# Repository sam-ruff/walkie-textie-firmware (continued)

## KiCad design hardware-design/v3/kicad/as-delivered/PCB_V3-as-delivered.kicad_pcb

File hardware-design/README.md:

# Hardware design

The board being worked on is the LoRa sensor node in `v3/kicad/` (V3.1). Its
own README says how to rebuild it and what to check before ordering, and
`CE_TESTING.md` beside it is how to run the compliance tests. No board has
been made from it yet.

`v3/` also holds the handover brief and the outside designer's drops that
V3.1 grew from. `archive/` holds the earlier radio boards and the scripts
that rebuilt the first of them. Nothing in there is current.

`CLAUDE.md` is the working log: what is settled and why, and the mistakes
made on the way.

KiCad 9 or newer is needed. The V3.1 tools use KiCad's `pcbnew` Python module
and were written against KiCad 10.0.8.

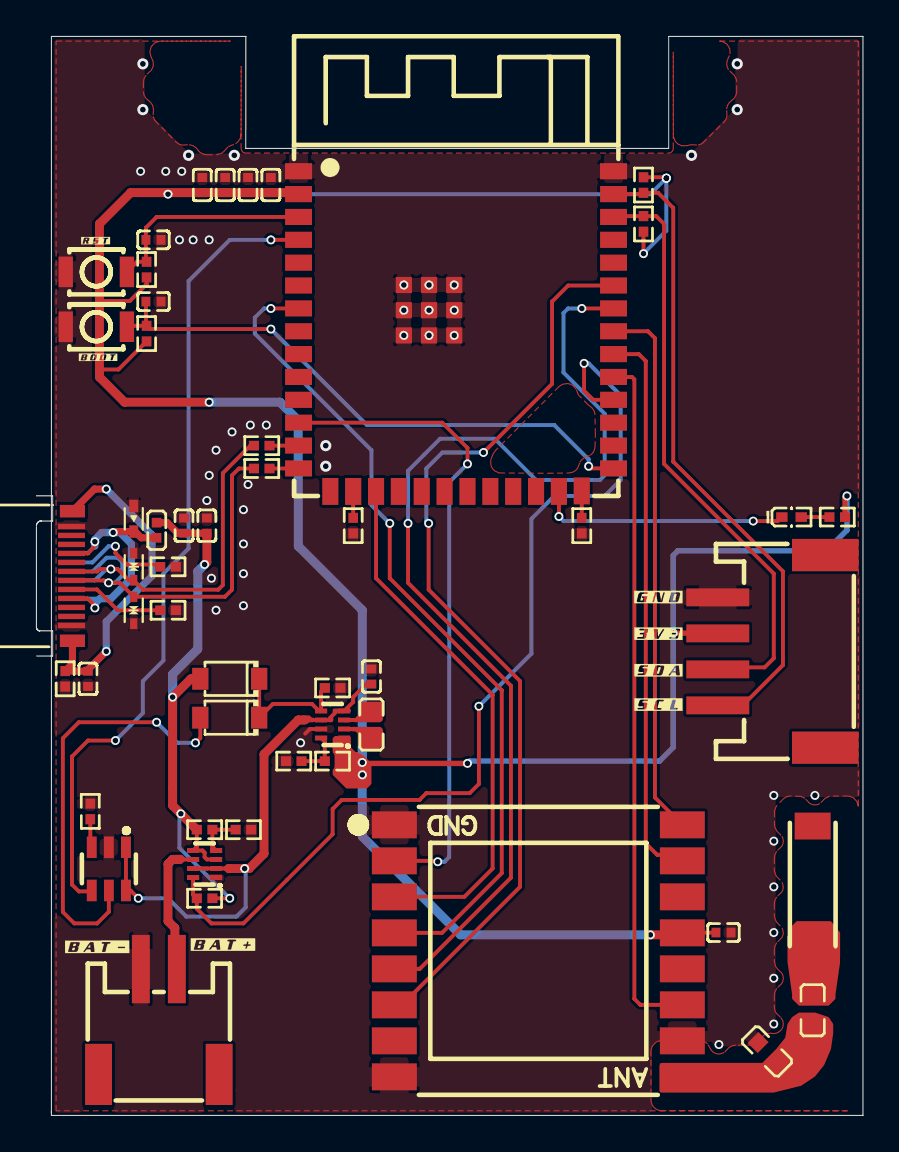
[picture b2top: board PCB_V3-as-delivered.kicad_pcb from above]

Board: 4 copper layers, 45.9 x 59.9 mm, 51 parts (0 on the bottom side), 40 nets.

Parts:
C1: 10uF; C0402
C3, C5, C7, C12, C13: 100nF; C0402
C4, C6, C9: 4.7uF; C0402
C25: 1nF; C0402
CN1: XY-S2B-PH-SM4-TB; CONN-SMD_P2.00_S2B-PH-SM4-TB-LF-SN
D1, D2: LESD5D5.0CT1G_C5199850; SOD-523_L1.2-W0.8-LS1.6-BI
D3: ESD5Z5; SOD-523_L1.2-W0.8-LS1.6-RD-2
L1: W3000; ANT-SMD_L7.0-W1.6
L2: 1uH; L0603
L3: 1KΩ; L0402
L5: 6.8nH; L0603
L6: 39nH; L0603
LED1: SZYY0402B; LED0402-RD_BLUE
R1, R2: 33Ω; R0402
R3, R4: 5.1kΩ; R0402
R5, R6, R8, R11, R12: 10kΩ; R0402
R7: 1kΩ; R0402
R9, R13: 47kΩ; R0402
R10: 1MΩ; R0402
R15: 511kΩ; R0402
R16: 91kΩ; R0402
R18, R19: 4.7kΩ; R0402
R20: 68kΩ; R0402
SW1, SW2: B3U-1000P; KEY-SMD_B3U-1000PM
U1: ESP32-S3-WROOM-1(N8R8); WIRELM-SMD_ESP32-S3-WROOM-1
U2: 1uF; C0402
U3: S4B-PH-SM4-TB(LF)(SN); CONN-SMD_S4B-PH-SM4-TB-LF-SN
U4: TPS2116DRLR; SOT-583-8_L2.1-W1.6-P0.50-LS1.6-BL
U5: TPS631000DRLR; SOT-583-8_L2.1-W1.2-P0.50-LS1.6-BL
U6: 15kΩ; R0402
U7, U9: B5819W_C2848199; SOD-123_L2.7-W1.6-LS3.7-RD
U8: TYPE-C 24P-GTJB 040; USB-C-SMD_TYPE-C-24P-GTJB-040
U10: TPL5111DDCR; TSOT-23-6_L2.9-W1.6-P0.95-LS2.8-BL
U11: SX1262S8S+T-X1; WIRELM-SMD_SX1278S165SY-T-X1

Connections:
3.3V_RAIL: C4.2, C9.2, C12.2, C13.2, R5.1, R6.1, R7.2, R15.2, R18.1, R19.1, U1.2, U2.2, U3.3, U5.1, U11.13
BAT+: CN1.2, U4.6
BOOT: C5.2, R6.2, SW1.1, U1.27
BUSY: U1.33, U11.16
CHS: C25.1, R10.1, U8.25, U8.26
D+: D1.1, R2.1, U8.A6, U8.B6
D-: D2.1, R1.1, U8.A7, U8.B7
DIO1: U1.32, U11.15
DONE: U1.4, U10.4
DRVN: U7.2, U10.5
EN: C3.2, R5.2, SW2.1, U1.3
GND: C1.1, C3.1, C4.1, C5.1, C6.1, C7.1, C9.1, C12.1, C13.1, C25.2, CN1.1, D1.2, D2.2, D3.2, L5.2, R3.1, R4.1, R10.2, R11.1, R12.1, R13.2, R16.2, R20.1, SW1.2, SW2.2, U1.1, U1.40, U1.41, U2.1, U3.4, U4.1, U5.7, U6.1, U8.A1, U8.A12, U8.B1, U8.B12, U10.2, U11.1, U11.8, U11.10
L1_1: L1.1, L6.2
LED1_2: LED1.2, R7.1
MISO: U1.12, U11.2
MOSI: U1.17, U11.3
NSS: U1.34, U11.5
R1_2: R1.2, U1.13
R2_2: R2.2, U1.14
R3_2: R3.2, U8.B5
R4_2: R4.2, U8.A5
RST: U1.35, U11.6
RXE: U1.31, U11.11
SCK: U1.7, U11.4
SCL: R19.2, U1.39, U3.1
SDA: R18.2, U1.38, U3.2
ST: R8.1, U1.30, U4.8
SYS_OUT: C1.2, U4.2, U4.7, U5.4, U5.6, U10.1, U10.6
U1_16: R11.2, U1.16
U1_26: R12.2, U1.26
U4_4: R9.1, U4.4, U6.2
U5_2: L2.2, U5.2
U5_3: L2.1, U5.3
U5_5: R13.1, U5.5, U7.1, U9.1
U5_8: R15.1, R16.1, U5.8
U10_3: R20.2, U10.3
U11_9: L5.1, L6.1, U11.9
USER_LED: LED1.1, U1.25
VBUS: C6.2, C7.2, L3.2, R8.2, R9.2, U4.3, U4.5, U9.2
VBUS_IN: D3.1, L3.1, U8.A4, U8.A9, U8.B4, U8.B9

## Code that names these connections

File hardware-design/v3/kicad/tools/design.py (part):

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part("R40", "1.5k", R0402, (8.75, 38.15), 90, {"1": "ILM", "2": "GND"}, lcsc="C25867", mpn="0402WGF1501TCE", manufacturer="UNI-ROYAL")

# ---------------------------------------------------------------- battery input and power mux
kept("CN1", "CN1", {"1": "BAT_RAW", "2": "GND", "3": "", "4": ""})     # pin order as the brief (B4)
# The brief names Vishay's Si2367DS, which JLCPCB does not stock. The Si2333DS is the same maker's
# 12 V part with the same pinout, and it is specified at the gate drive two tired AA cells give:
# 59 milliohms at 1.8 V, with 100 nA gate leakage.
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# wire-wound part with 0.26 ohms of resistance; the drop's multilayer 39 nH has 1 ohm, a Q of 12 at
# 100 MHz and a self-resonance that can be as low as 1.4 GHz. L5 only shunts the feed, and JLCPCB holds
# no wire-wound 6.8 nH in numbers, so it stays as the drop had it.
kept("L6", "L6", {"1": "ANT_FEED", "2": "RF_FEED"}, at=(32.0, 9.5), rot=90,
     value="39nH", lcsc="C86134", mpn="LQW18AN39NG00D", manufacturer="Murata")
part("L7", "DNP", L0603, (30.3, 9.5), 90, {"1": "ANT_FEED", "2": "GND"}, dnp=True)
part("ANT1", "W3000", (LIB_NEW, "Pulse_W3000"), (35.3, 1.3), 0, {"1": "ANT_FEED", "2": "ANT_TUNE"},
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
    # USB input protection: bead -> C7 and U14's input pins -> U14 -> VBUS
    (T, "VBUS_F", "top", 0.4, [(5.84, 33.297), (5.84, 35.25), (6.85, 35.25)]),
    (T, "VBUS_F", "top", 0.25, [(6.85, 35.25), (6.85, 35.75)]),                                  # both input pins
    (T, "VBUS_F", "top", 0.2, [(5.84, 35.25), (5.84, 35.55), (4.971, 35.55), (4.971, 36.25)]),   # R38
    (T, "UVLO", "top", 0.2, [(5.837, 36.25), (6.85, 36.25)]),
    (T, "UVLO", "top", 0.2, [(5.837, 36.25), (5.837, 37.121)]),                                  # R39
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
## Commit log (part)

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2025-12-06 feat(api): initial commit
2025-12-06 Removed target directory
2025-12-06 fix: Updated rust action
2025-12-06 Notes added by 'git notes add'
2025-12-06 fix: Updated README and made actions skip on chores
2025-12-06 fix: Working BLE implementation and tests
2025-12-06 fix: Made the recieving more reliable and added ble to ble tests
2025-12-14 fix: Minor fixes
2025-12-14 fix: Moved embassy tasks to tasks module
2025-12-14 fix: Working debug logging
2025-12-15 fix: Added debug for version and reboot command and fixed github actions.
2025-12-15 fix: updated README with commands
2025-12-15 fix: Fixed a number of warnings and made clippy happy
2025-12-15 fix: Removed serial module
2025-12-15 fix: Fixed some missing packages and removed log
2025-12-15 fix: Updated how debugging works
2025-12-15 fix: Updated tests and flash devices
2026-06-19 chore(lora): WIP calibration and driver updates
2026-06-19 refactor(protocol): use shared wt-protocol crate for the wire codec
    Replace the in-tree commands/ and protocol/ modules with the shared
    wt-protocol crate, vendored as a git submodule, so the firmware and the
    phone app share one COBS/CRC command-response codec and cannot drift.
    - swap CommandParser/ResponseSerialiser for wt_protocol::{parse_command,
    encode_response, cobs_decode} in the serial and BLE tasks
    - FrameAccumulator now yields frames including the trailing delimiter,
